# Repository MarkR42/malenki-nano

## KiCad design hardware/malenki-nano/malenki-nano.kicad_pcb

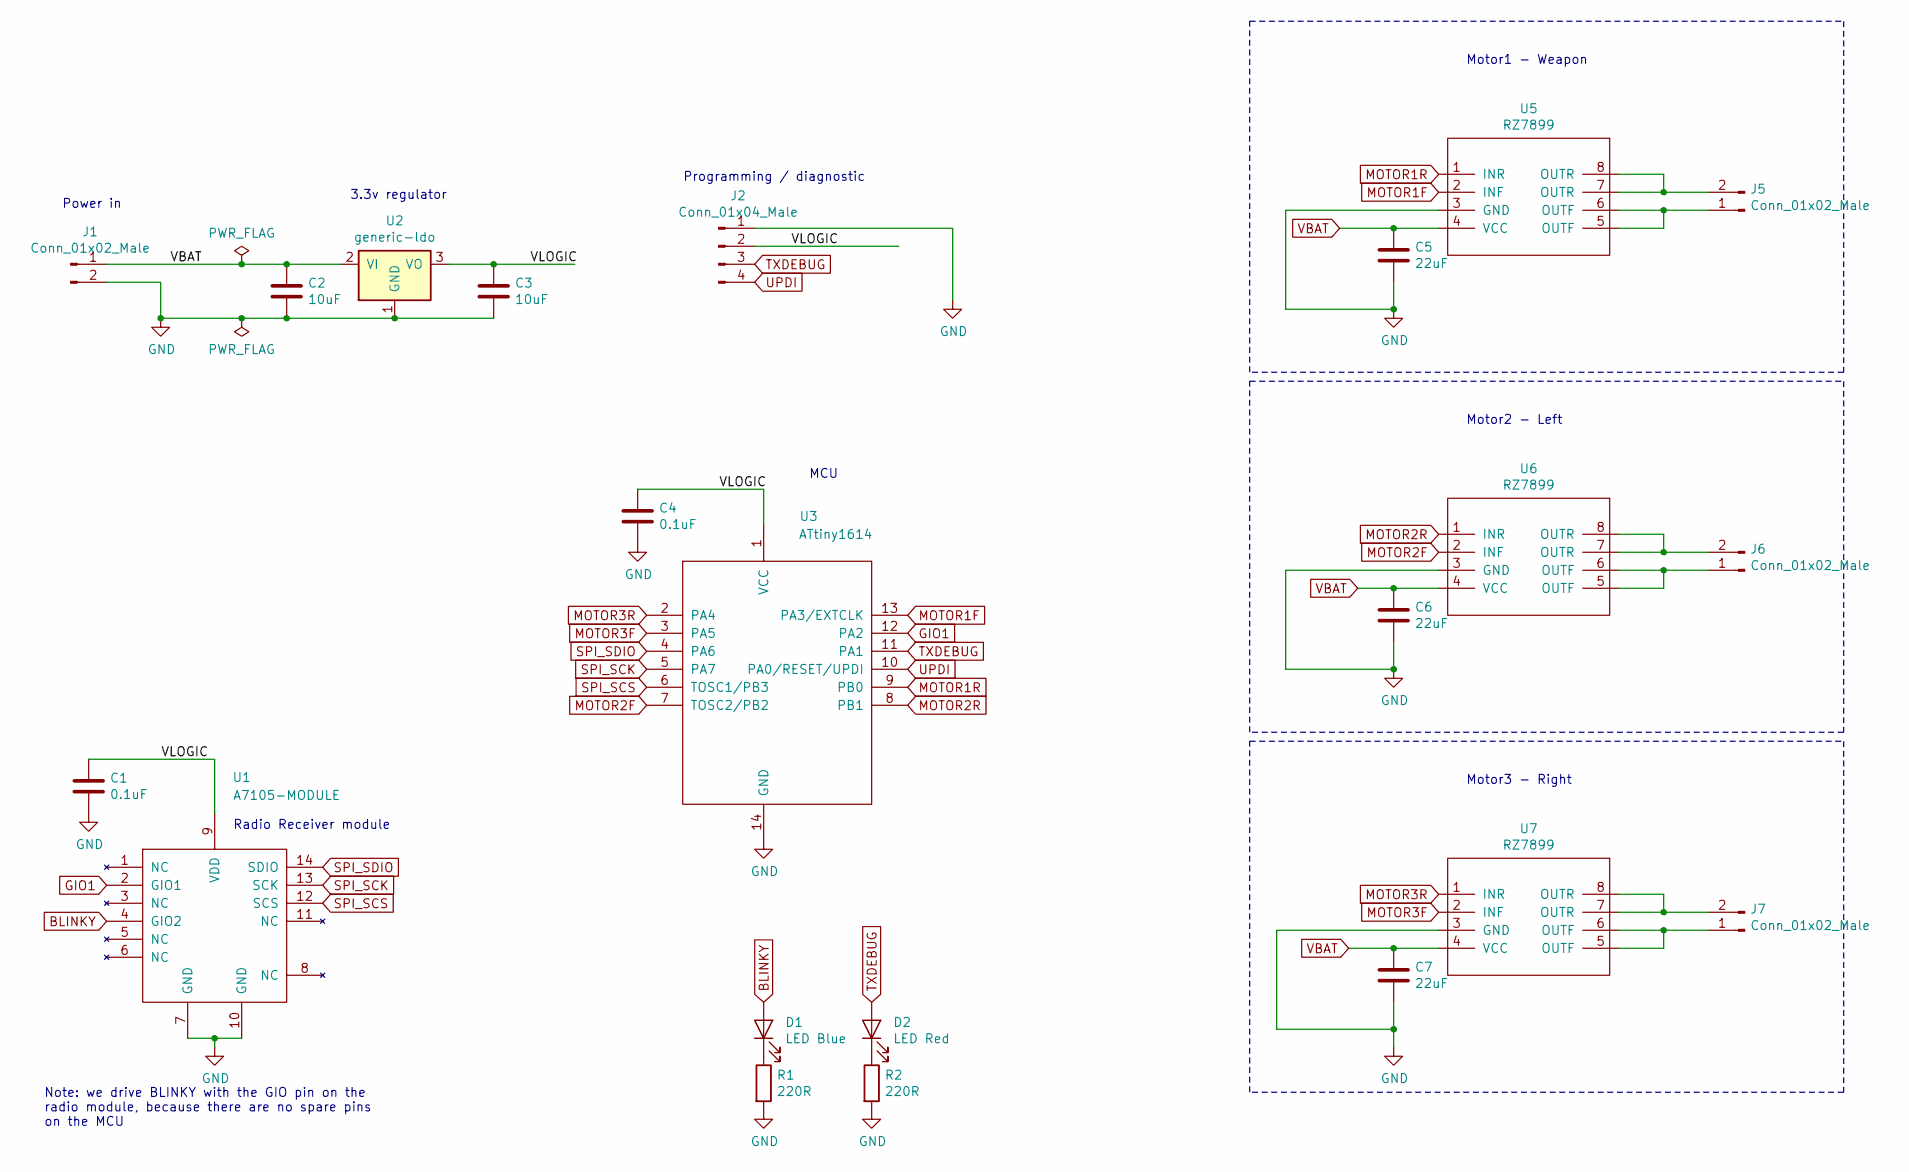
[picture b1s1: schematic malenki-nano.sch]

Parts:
C1, C4: 0.1uF; C_0805_2012Metric
C2, C3: 10uF; C_0805_2012Metric
C5, C6, C7: 22uF; C_1206_3216Metric
D1: LED Blue; LED_1206_3216Metric_Castellated
D2: LED Red; LED_1206_3216Metric_Castellated
J1, J5, J6, J7: Conn_01x02_Male; PinHeader_1x02_P2.54mm_BIG1
J2: Conn_01x04_Male; PinHeader_1x04_P2.00mm_Vertical
R1, R2: 220R; R_0805_2012Metric
U1: A7105-MODULE; A7105-module
U2: generic-ldo; SOT-89-3
U3: ATtiny1614; SOIC-14_3.9x8.7mm_P1.27mm
U5, U6, U7: RZ7899; SOIC-8_3.9x4.9mm_P1.27mm

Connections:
/VLOGIC: C1.1, C3.1, C4.1, J2.2, U1.9 (VDD), U2.3 (VO), U3.1 (VCC)
BLINKY: D1.2 (A), U1.4 (GIO2)
GIO1: U1.2 (GIO1), U3.12 (PA2)
GND: C1.2, C2.2, C3.2, C4.2, C5.2, C6.2, C7.2, J1.2, J2.1, R1.2, R2.2, U1.7 (GND), U1.10 (GND), U2.1 (GND), U3.14 (GND), U5.3 (GND), U6.3 (GND), U7.3 (GND)
MOTOR1F: U3.13 (PA3/EXTCLK), U5.2 (INF)
MOTOR1R: U3.9 (PB0), U5.1 (INR)
MOTOR2F: U3.7 (TOSC2/PB2), U6.2 (INF)
MOTOR2R: U3.8 (PB1), U6.1 (INR)
MOTOR3F: U3.3 (PA5), U7.2 (INF)
MOTOR3R: U3.2 (PA4), U7.1 (INR)
unnamed: D1.1 (K), R1.1
unnamed: D2.1 (K), R2.1
unnamed: J5.1, U5.5 (OUTF), U5.6 (OUTF)
unnamed: J5.2, U5.7 (OUTR), U5.8 (OUTR)
unnamed: J6.1, U6.5 (OUTF), U6.6 (OUTF)
unnamed: J6.2, U6.7 (OUTR), U6.8 (OUTR)
unnamed: J7.1, U7.5 (OUTF), U7.6 (OUTF)
unnamed: J7.2, U7.7 (OUTR), U7.8 (OUTR)
SPI_SCK: U1.13 (SCK), U3.5 (PA7)
SPI_SCS: U1.12 (SCS), U3.6 (TOSC1/PB3)
SPI_SDIO: U1.14 (SDIO), U3.4 (PA6)
TXDEBUG: D2.2 (A), J2.3, U3.11 (PA1)
UPDI: J2.4, U3.10 (PA0/RESET/UPDI)
VBAT: C2.1, C5.1, C6.1, C7.1, J1.1, U2.2 (VI), U5.4 (VCC), U6.4 (VCC), U7.4 (VCC)

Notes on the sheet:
Power in
3.3v regulator
Radio Receiver module
MCU
Programming / diagnostic
Note: we drive BLINKY with the GIO pin on the radio module, because there are no spare pins on the MCU
Motor1 - Weapon
Motor2 - Left
Motor3 - Right

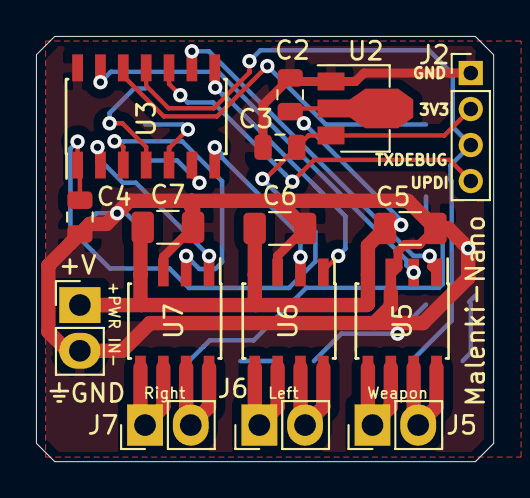
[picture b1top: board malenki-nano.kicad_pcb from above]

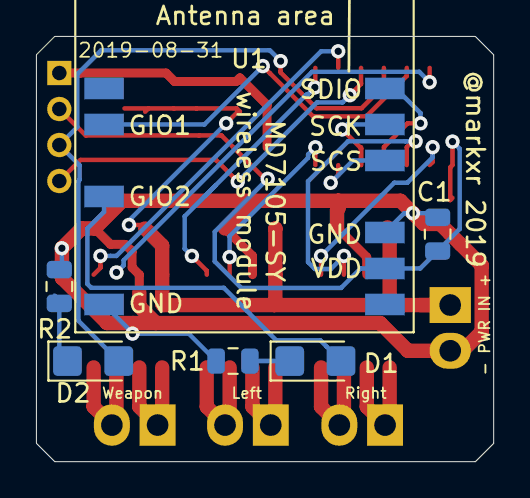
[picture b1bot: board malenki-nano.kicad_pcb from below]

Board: 2 copper layers, 25.4 x 23.6 mm, 22 parts (6 on the bottom side), 24 nets.

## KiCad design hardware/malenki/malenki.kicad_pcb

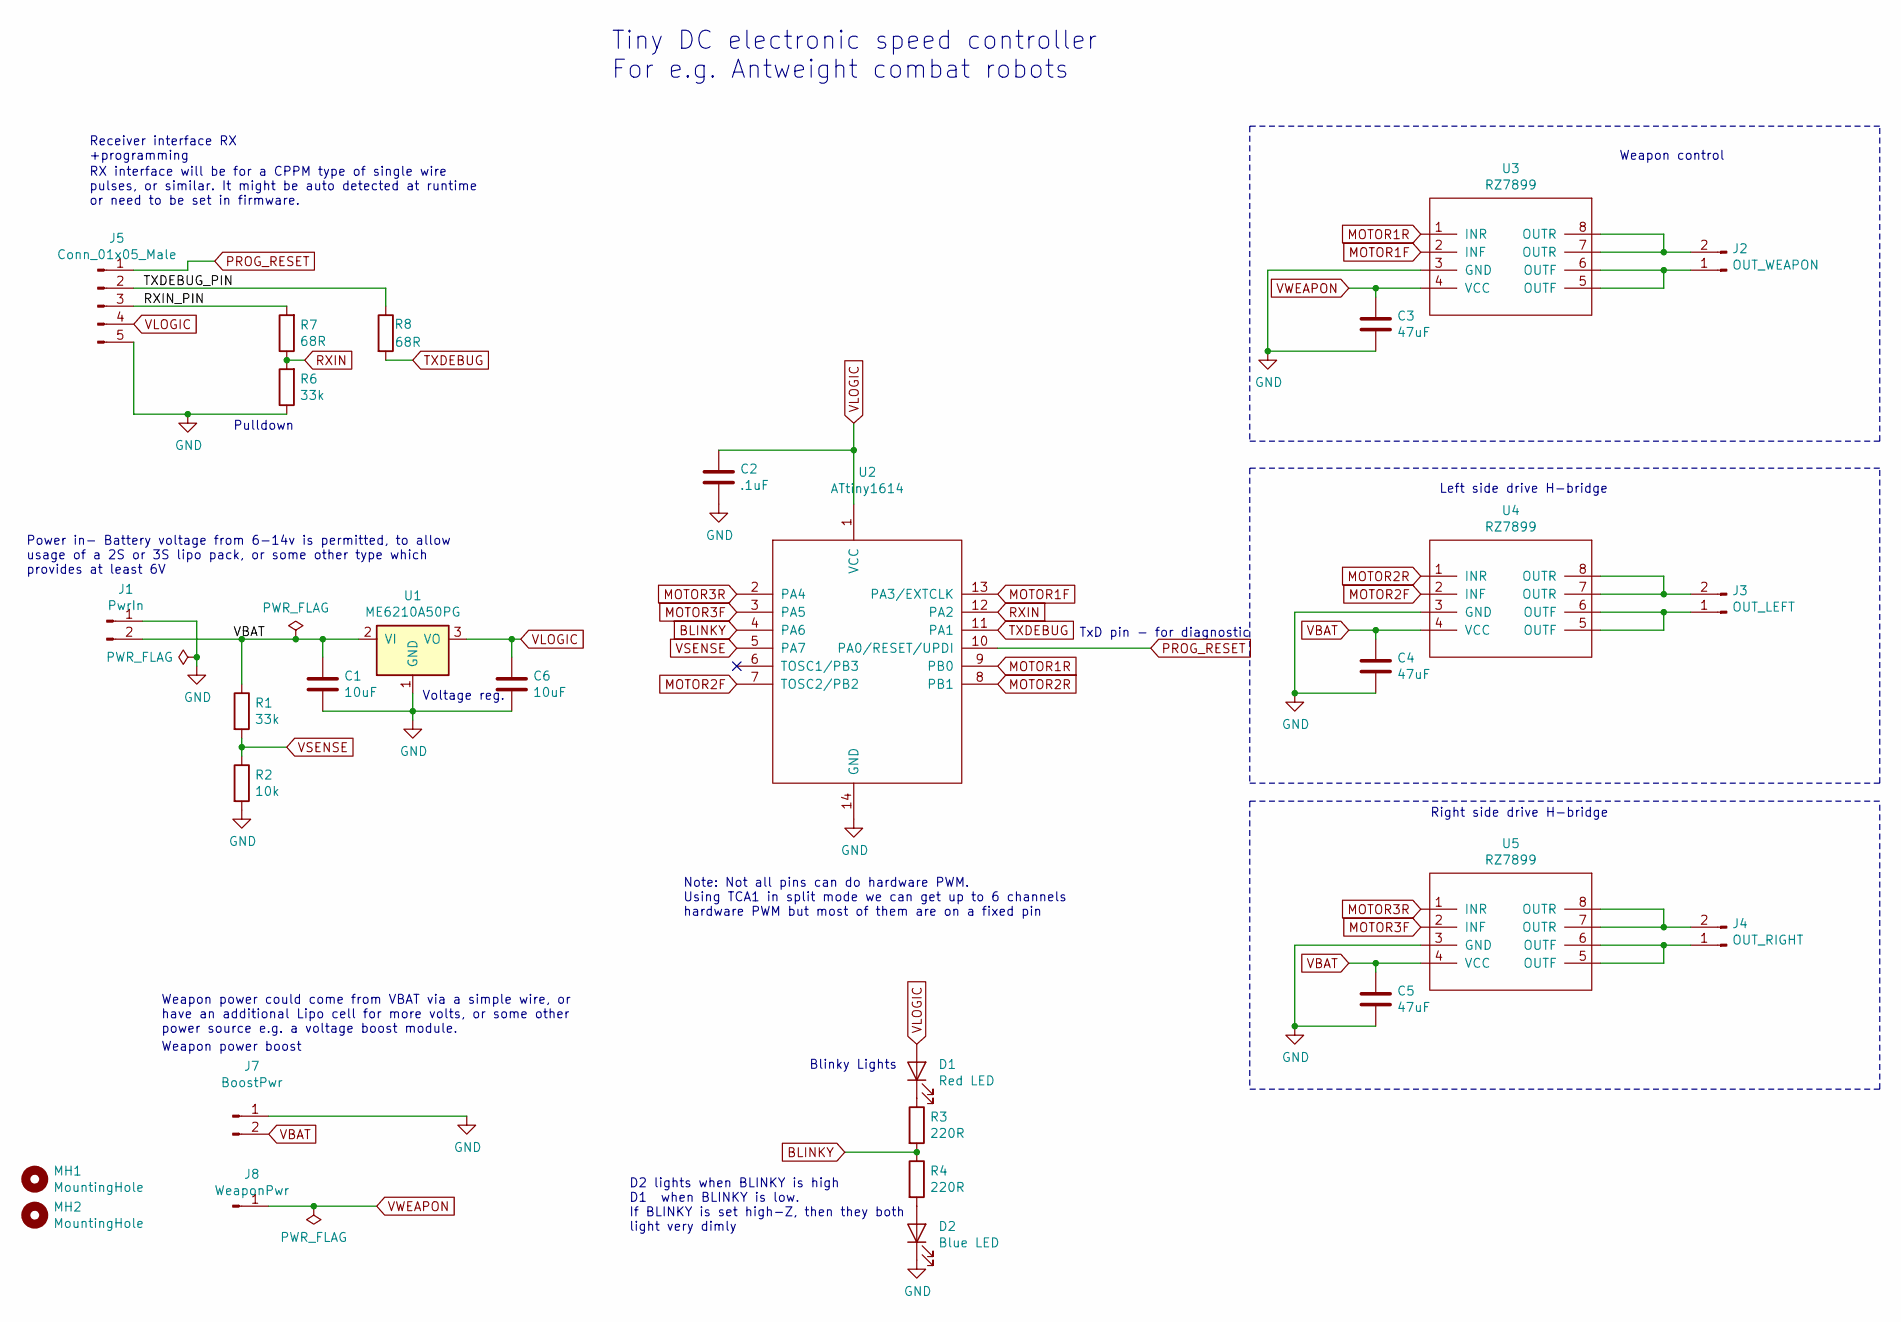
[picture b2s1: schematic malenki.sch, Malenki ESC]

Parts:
C1, C6: 10uF; C_0805_2012Metric_Pad1.15x1.40mm_HandSolder
C2: .1uF; C_0805_2012Metric_Pad1.15x1.40mm_HandSolder
C3, C4, C5: 47uF; C_1206_3216Metric
D1: Red LED; LED_0805_2012Metric_Castellated
D2: Blue LED; LED_0805_2012Metric_Castellated
J1: PwrIn; PinHeader_1x02_P2.54mm_BIG1
J2: OUT_WEAPON; PinHeader_1x02_P2.54mm_BIG1
J3: OUT_LEFT; PinHeader_1x02_P2.54mm_BIG1
J4: OUT_RIGHT; PinHeader_1x02_P2.54mm_BIG1
J5: Conn_01x05_Male; PinHeader_1x05_P2.54mm_BIG1
J7: BoostPwr; PinHeader_1x02_P2.54mm_BIG1
J8: WeaponPwr; PinHeader_1_BIG1
MH1, MH2: MountingHole; MountingHole_2.2mm_M2
R1, R6: 33k; R_0805_2012Metric
R2: 10k; R_0805_2012Metric
R3, R4: 220R; R_0805_2012Metric
R7, R8: 68R; R_0805_2012Metric
U1: ME6210A50PG; SOT-89-3
U2: ATtiny1614; SOIC-14_3.9x8.7mm_P1.27mm
U3, U4, U5: RZ7899; SOIC-8_3.9x4.9mm_P1.27mm

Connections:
/RXIN_PIN: J5.3, R7.2
/TXDEBUG_PIN: J5.2, R8.1
BLINKY: R3.2, R4.1, U2.4 (PA6)
GND: C1.2, C2.2, C3.2, C4.2, C5.2, C6.2, D2.1 (K), J1.1, J5.5, J7.1, R2.2, R6.1, U1.1 (GND), U2.14 (GND), U3.3 (GND), U4.3 (GND), U5.3 (GND)
MOTOR1F: U2.13 (PA3/EXTCLK), U3.2 (INF)
MOTOR1R: U2.9 (PB0), U3.1 (INR)
MOTOR2F: U2.7 (TOSC2/PB2), U4.2 (INF)
MOTOR2R: U2.8 (PB1), U4.1 (INR)
MOTOR3F: U2.3 (PA5), U5.2 (INF)
MOTOR3R: U2.2 (PA4), U5.1 (INR)
unnamed: D1.1 (K), R3.1
unnamed: D2.2 (A), R4.2
unnamed: J2.1, U3.5 (OUTF), U3.6 (OUTF)
unnamed: J2.2, U3.7 (OUTR), U3.8 (OUTR)
unnamed: J3.1, U4.5 (OUTF), U4.6 (OUTF)
unnamed: J3.2, U4.7 (OUTR), U4.8 (OUTR)
unnamed: J4.1, U5.5 (OUTF), U5.6 (OUTF)
unnamed: J4.2, U5.7 (OUTR), U5.8 (OUTR)
PROG_RESET: J5.1, U2.10 (PA0/RESET/UPDI)
RXIN: R6.2, R7.1, U2.12 (PA2)
TXDEBUG: R8.2, U2.11 (PA1)
VBAT: C1.1, C4.1, C5.1, J1.2, J7.2, R1.1, U1.2 (VI), U4.4 (VCC), U5.4 (VCC)
VLOGIC: C2.1, C6.1, D1.2 (A), J5.4, U1.3 (VO), U2.1 (VCC)
VSENSE: R1.2, R2.1, U2.5 (PA7)
VWEAPON: C3.1, J8.1, U3.4 (VCC)

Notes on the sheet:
Receiver interface RX +programming
Pulldown
Weapon control
Weapon power boost
Blinky Lights
TxD pin - for diagnostic
Power in- Battery voltage from 6-14v is permitted, to allow usage of a 2S or 3S lipo pack, or some other type which provides at least 6V
RX interface will be for a CPPM type of single wire pulses, or similar. It might be auto detected at runtime or need to be set in firmware.
Voltage reg.
Weapon power could come from VBAT via a simple wire, or have an additional Lipo cell for more volts, or some other power source e.g. a voltage boost module.
D2 lights when BLINKY is high D1 when BLINKY is low. If BLINKY is set high-Z, then they both light very dimly
Left side drive H-bridge
Right side drive H-bridge
Note: Not all pins can do hardware PWM. Using TCA1 in split mode we can get up to 6 channels hardware PWM but most of them are on a fixed pin
Tiny DC electronic speed controller For e.g. Antweight combat robots

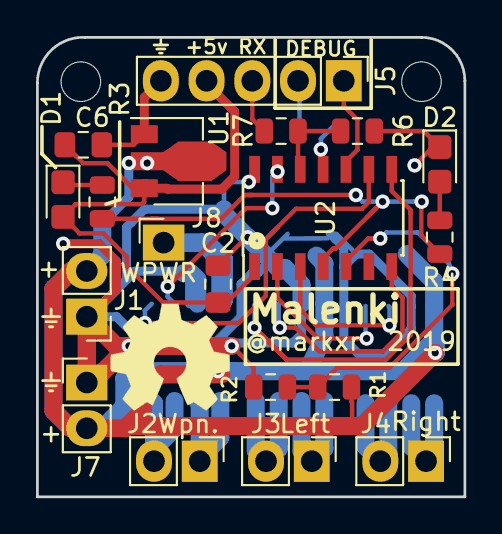
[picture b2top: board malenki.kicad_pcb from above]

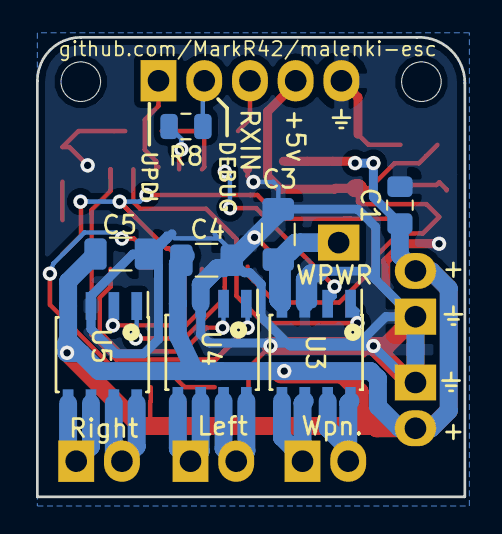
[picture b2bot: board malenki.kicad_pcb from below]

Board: 2 copper layers, 23.8 x 25.5 mm, 29 parts (8 on the bottom side), 25 nets.

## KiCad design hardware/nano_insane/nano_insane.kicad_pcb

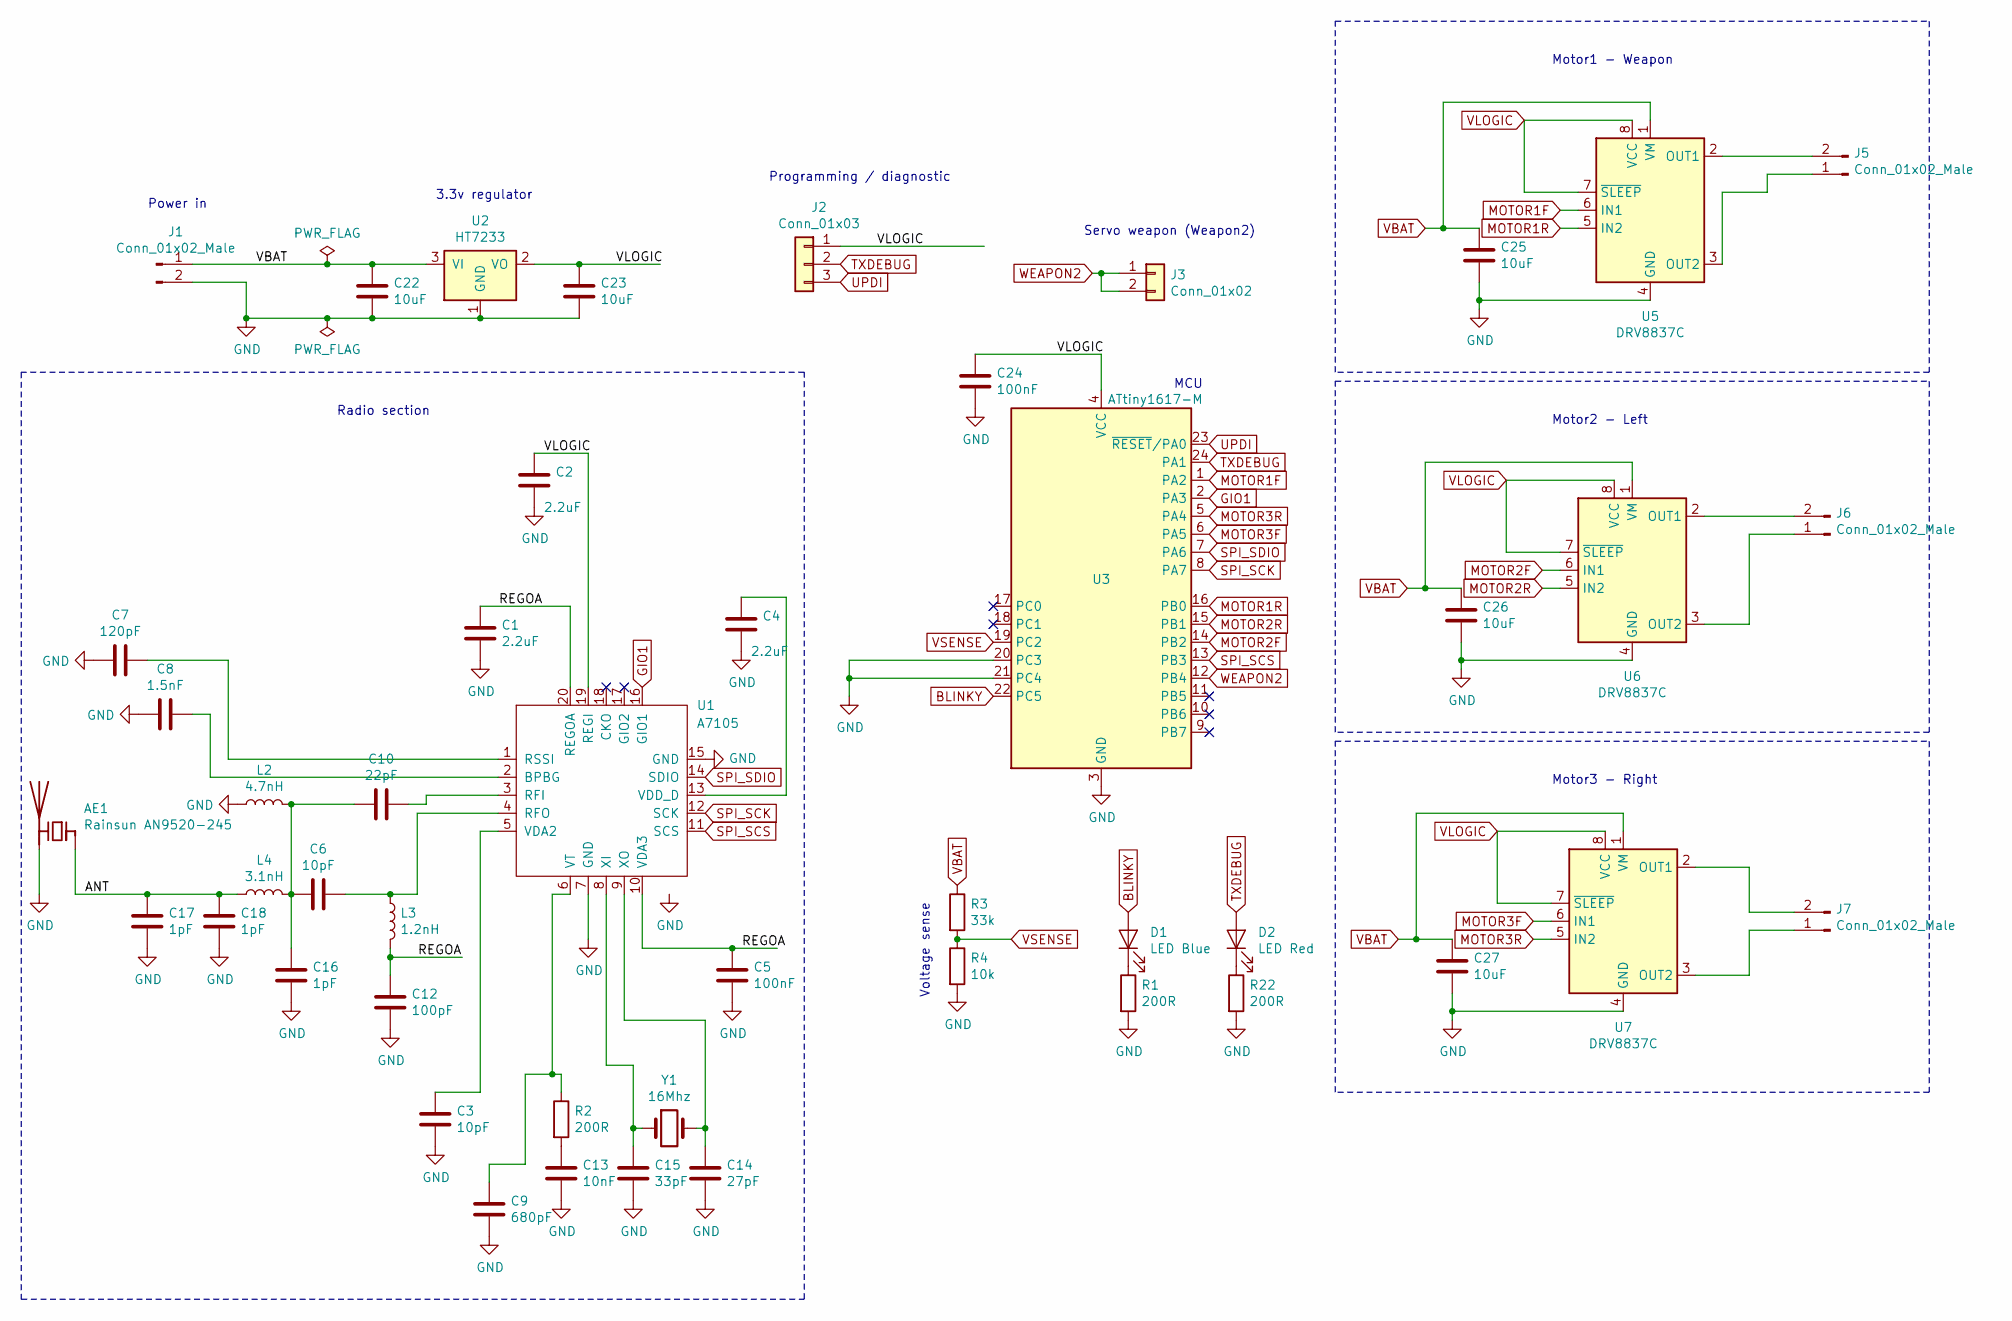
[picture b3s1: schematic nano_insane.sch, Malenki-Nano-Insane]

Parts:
AE1: Rainsun AN9520-245; Rainsun_AN9520
C1, C2, C4: 2.2uF; C_0402_1005Metric
C3, C6: 10pF; C_0402_1005Metric
C5: 100nF; C_0402_1005Metric
C7: 120pF; C_0402_1005Metric
C8: 1.5nF; C_0402_1005Metric
C9: 680pF; C_0402_1005Metric
C10: 22pF; C_0402_1005Metric
C12: 100pF; C_0402_1005Metric
C13: 10nF; C_0402_1005Metric
C14: 27pF; C_0402_1005Metric
C15: 33pF; C_0402_1005Metric
C16, C17, C18: 1pF; C_0402_1005Metric
C22, C23, C25, C26, C27: 10uF; C_0603_1608Metric; LCSC C19702
C24: 100nF; C_0402_1005Metric; Partnum C14663; LCSC C14663
D1: LED Blue; LED_0805_2012Metric_Castellated; LCSC C72035
D2: LED Red; LED_0805_2012Metric_Castellated; LCSC C84256
J1, J5, J6, J7: Conn_01x02_Male; PinHeader_1x02_P2.54mm_BIG1
J2: Conn_01x03; PinHeader_1x03_P2.00mm_Vertical
J3: Conn_01x02; wirepad_2
L2: 4.7nH; L_0402_1005Metric
L3: 1.2nH; L_0402_1005Metric
L4: 3.1nH; L_0402_1005Metric
R1, R2, R22: 200R; R_0402_1005Metric; Partnum C22962; LCSC C22962
R3: 33k; R_0402_1005Metric; Partnum C4216; LCSC C4216
R4: 10k; R_0402_1005Metric; Partnum C25804; LCSC C25804
U1: A7105; A7105_QFN-20
U2: HT7233; SOT-23; Partnum C211659; LCSC C211659
U3: ATtiny1617-M; qfn24-hand1; Partnum C194193; LCSC C194193
U5, U6, U7: DRV8837C; WSON-8-1EP_2x2mm_P0.5mm_HAND1; LCSC C39159
Y1: 16Mhz; Crystal_SMD_5032-2Pin_5.0x3.2mm

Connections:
/ANT: AE1.1 (FEED), C17.2, C18.2, L4.1
/REGOA: C1.2, C5.2, C12.2, L3.2, U1.10 (VDA3), U1.20 (REGOA)
BLINKY: D1.2 (A), U3.22 (PC5)
GIO1: U1.16 (GIO1), U3.2 (PA3)
GND: AE1.2 (PCB_Trace), C1.1, C2.1, C3.1, C4.1, C5.1, C7.2, C8.2, C9.1, C12.1, C13.1, C14.1, C15.1, C16.1, C17.1, C18.1, C22.2, C23.2, C24.2, C25.2, C26.2, C27.2, J1.2, L2.1, R1.2, R4.2, R22.2, U1.7 (GND), U1.15 (GND), U1.21 (GND), U2.1 (GND), U3.3 (GND), U3.20 (PC3), U3.21 (PC4), U3.25 (GND), U5.4 (GND), U5.9 (GND), U6.4 (GND), U6.9 (GND), U7.4 (GND), U7.9 (GND)
MOTOR1F: U3.1 (PA2), U5.6 (IN1)
MOTOR1R: U3.16 (PB0), U5.5 (IN2)
MOTOR2F: U3.14 (PB2), U6.6 (IN1)
MOTOR2R: U3.15 (PB1), U6.5 (IN2)
MOTOR3F: U3.6 (PA5), U7.6 (IN1)
MOTOR3R: U3.5 (PA4), U7.5 (IN2)
unnamed: C3.2, U1.5 (VDA2)
unnamed: C4.2, U1.13 (VDD_D)
unnamed: C6.1, L3.1, U1.4 (RFO)
unnamed: C7.1, U1.1 (RSSI)
unnamed: C8.1, U1.2 (BPBG)
unnamed: C9.2, R2.1, U1.6 (VT)
unnamed: C10.1, U1.3 (RFI)
unnamed: C6.2, C10.2, C16.2, L2.2, L4.2
unnamed: C13.2, R2.2
unnamed: C14.2, U1.9 (XO), Y1.2
unnamed: C15.2, U1.8 (XI), Y1.1
unnamed: D1.1 (K), R1.1
unnamed: D2.1 (K), R22.1
unnamed: J5.1, U5.3 (OUT2)
unnamed: J5.2, U5.2 (OUT1)
unnamed: J6.1, U6.3 (OUT2)
unnamed: J6.2, U6.2 (OUT1)
unnamed: J7.1, U7.3 (OUT2)
unnamed: J7.2, U7.2 (OUT1)
SPI_SCK: U1.12 (SCK), U3.8 (PA7)
SPI_SCS: U1.11 (SCS), U3.13 (PB3)
SPI_SDIO: U1.14 (SDIO), U3.7 (PA6)
TXDEBUG: D2.2 (A), J2.2, U3.24 (PA1)
UPDI: J2.3, U3.23 (~RESET~/PA0)
VBAT: C22.1, C25.1, C26.1, C27.1, J1.1, R3.1, U2.3 (VI), U5.1 (VM), U6.1 (VM), U7.1 (VM)
VLOGIC: C2.2, C23.1, C24.1, J2.1, U1.19 (REGI), U2.2 (VO), U3.4 (VCC), U5.7 (~SLEEP), U5.8 (VCC), U6.7 (~SLEEP), U6.8 (VCC), U7.7 (~SLEEP), U7.8 (VCC)
VSENSE: R3.2, R4.1, U3.19 (PC2)
WEAPON2: J3.1, J3.2, U3.12 (PB4)

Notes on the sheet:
Power in
3.3v regulator
MCU
Programming / diagnostic
Motor1 - Weapon
Motor2 - Left
Motor3 - Right
Servo weapon (Weapon2)
Voltage sense
Radio section

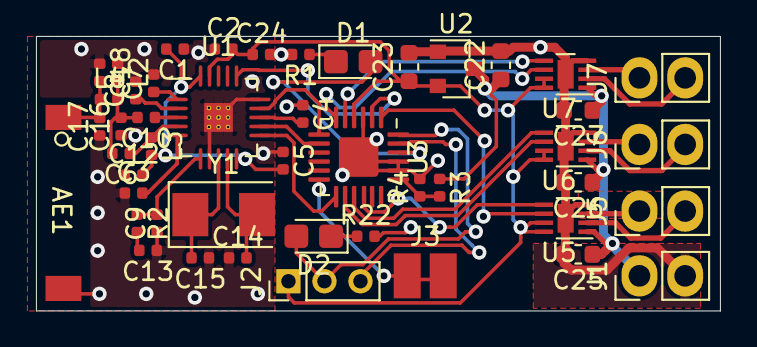
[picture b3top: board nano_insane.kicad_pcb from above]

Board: 2 copper layers, 38.0 x 15.2 mm, 47 parts (0 on the bottom side), 39 nets.
